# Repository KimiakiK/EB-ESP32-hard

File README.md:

# EB-ESP32
- [ESP32本体](https://github.com/KimiakiK/DIP-ESP32-hard)
- [ESP32用デバッガ](https://github.com/KimiakiK/DBG-ESP32-hard)
- [フルカラーLED付きロータリーエンコーダ](https://akizukidenshi.com/catalog/g/gP-05773/)
- [カラーディスプレイ TFT 1.3inch 240x240 ATM0130B3](https://akizukidenshi.com/catalog/g/gK-15560/)
- [キャラクタディスプレイ LCD 16x2 AQM1602Y-RN-GBW](https://akizukidenshi.com/catalog/g/gP-11916/)
- [温湿度・気圧センサ BME280](https://akizukidenshi.com/catalog/g/gK-09421/)
- [CO2センサ MH-Z19C](https://akizukidenshi.com/catalog/g/gM-16142/)
- [照度センサ NJL7502L](https://akizukidenshi.com/catalog/g/gI-02325/)
- [Micro SD カードコネクタ DM3AT-SF-PEJM5](https://akizukidenshi.com/catalog/g/gK-05488/)
- [リアルタイムクロック RTC IC RX8900 DIP AE-RX8900](https://akizukidenshi.com/catalog/g/gK-13009)

# Photos

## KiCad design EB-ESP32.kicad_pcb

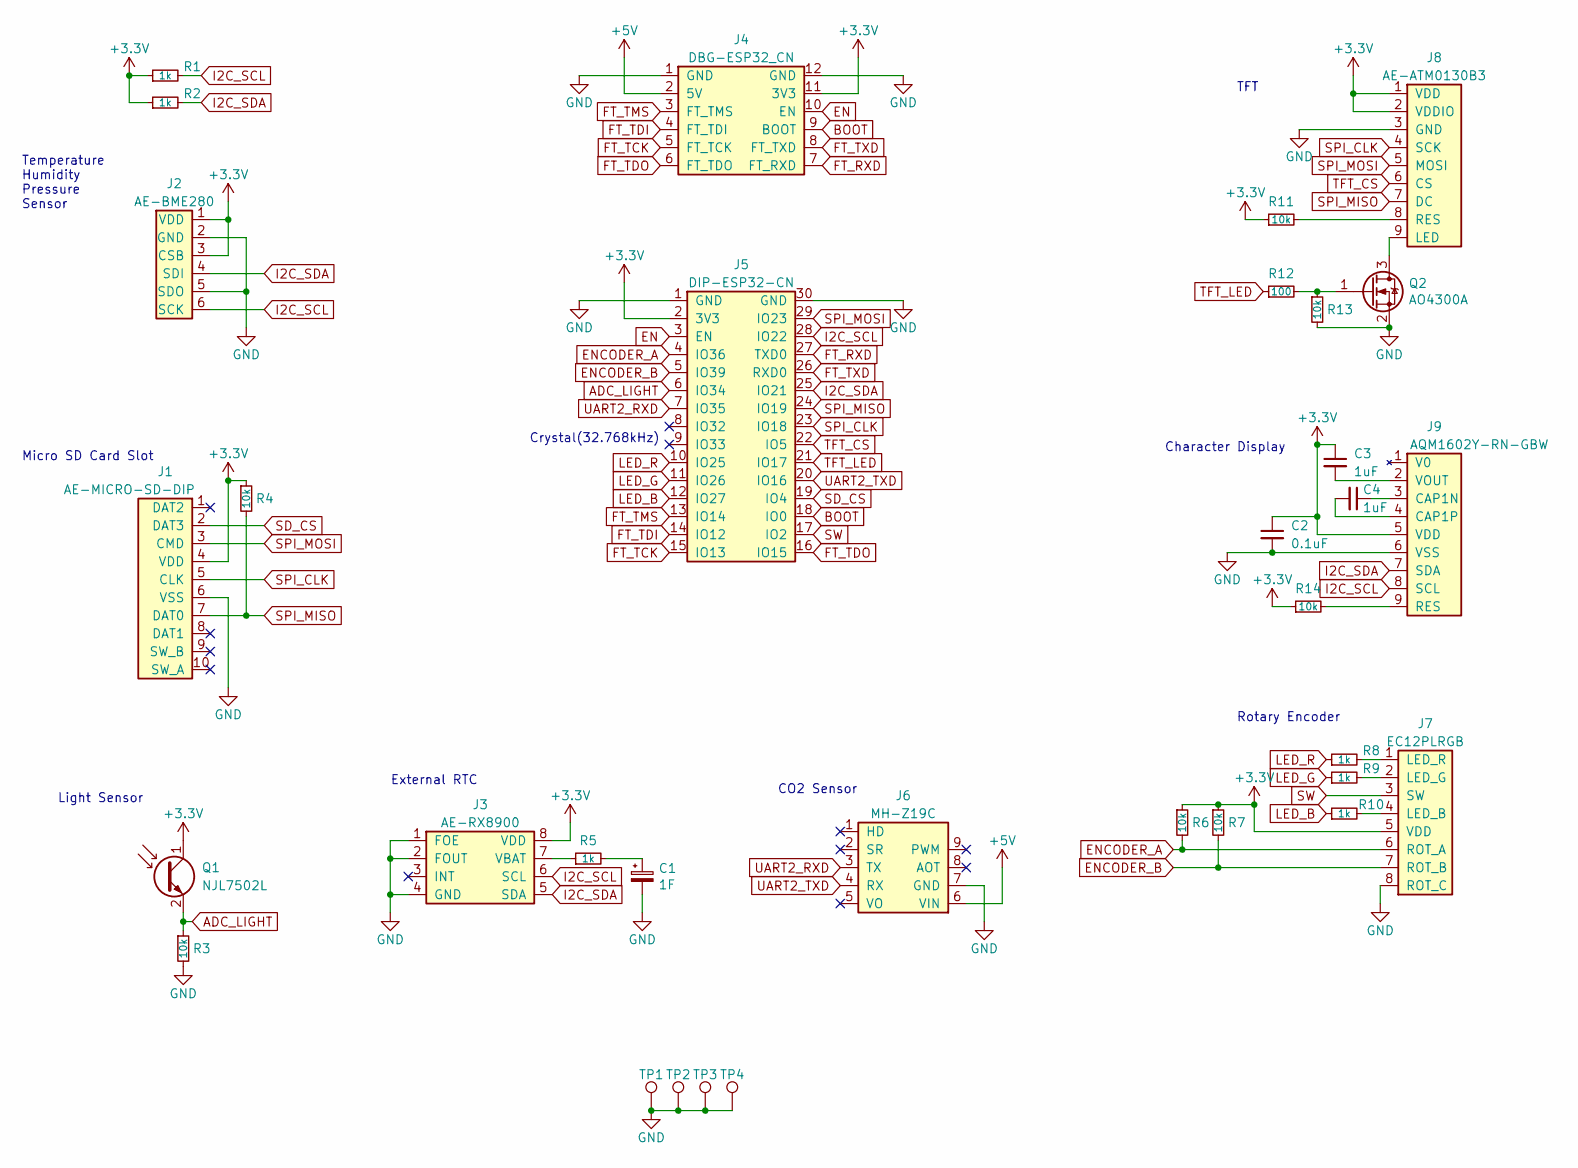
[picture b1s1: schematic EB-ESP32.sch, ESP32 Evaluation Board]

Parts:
C1: 1F; SE-5R5-D105VY
C2: 0.1uF; 1608Metric
C3, C4: 1uF; 1608Metric
J1: AE-MICRO-SD-DIP
J2: AE-BME280
J3: AE-RX8900
J4: DBG-ESP32_CN; DBG-ESP32-CN
J5: DIP-ESP32-CN
J6: MH-Z19C
J7: EC12PLRGB
J8: AE-ATM0130B3
J9: AQM1602Y-RN-GBW
Q1: NJL7502L
Q2: AO4300A; SOT-23
R1, R2, R5, R8, R9, R10: 1k; 1608Metric
R3, R4, R6, R7, R11, R13, R14: 10k; 1608Metric
R12: 100; 1608Metric
TP1, TP2, TP3, TP4: TestPoint; GND_PAD

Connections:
+3V3: C2.1, C3.1, J1.4 (VDD), J2.1 (VDD), J2.3 (CSB), J3.8 (VDD), J4.11 (3V3), J5.2 (3V3), J7.5 (VDD), J8.1 (VDD), J8.2 (VDDIO), J9.5 (VDD), Q1.1 (C), R1.1, R2.1, R4.1, R6.1, R7.1, R11.1, R14.1
+5V: J4.2 (5V), J6.6 (VIN)
ADC_LIGHT: J5.6 (IO34), Q1.2 (E), R3.1
BOOT: J4.9 (BOOT), J5.18 (IO0)
EN: J4.10 (EN), J5.3 (EN)
ENCODER_A: J5.4 (IO36), J7.6 (ROT_A), R6.2
ENCODER_B: J5.5 (IO39), J7.7 (ROT_B), R7.2
FT_RXD: J4.7 (FT_RXD), J5.27 (TXD0)
FT_TCK: J4.5 (FT_TCK), J5.15 (IO13)
FT_TDI: J4.4 (FT_TDI), J5.14 (IO12)
FT_TDO: J4.6 (FT_TDO), J5.16 (IO15)
FT_TMS: J4.3 (FT_TMS), J5.13 (IO14)
FT_TXD: J4.8 (FT_TXD), J5.26 (RXD0)
GND: C1.2, C2.2, J1.6 (VSS), J2.2 (GND), J2.5 (SDO), J3.1 (FOE), J3.2 (FOUT), J3.4 (GND), J4.1 (GND), J4.12 (GND), J5.1 (GND), J5.30 (GND), J6.7 (GND), J7.8 (ROT_C), J8.3 (GND), J9.6 (VSS), Q2.2 (S), R3.2, R13.2, TP1.1, TP2.1, TP3.1, TP4.1
I2C_SCL: J2.6 (SCK), J3.6 (SCL), J5.28 (IO22), J9.8 (SCL), R1.2
I2C_SDA: J2.4 (SDI), J3.5 (SDA), J5.25 (IO21), J9.7 (SDA), R2.2
LED_B: J5.12 (IO27), R10.1
LED_G: J5.11 (IO26), R9.1
LED_R: J5.10 (IO25), R8.1
unnamed: C1.1, R5.2
unnamed: C3.2, J9.2 (VOUT)
unnamed: C4.1, J9.3 (CAP1N)
unnamed: C4.2, J9.4 (CAP1P)
unnamed: J3.7 (VBAT), R5.1
unnamed: J7.1 (LED_R), R8.2
unnamed: J7.2 (LED_G), R9.2
unnamed: J7.4 (LED_B), R10.2
unnamed: J8.8 (RES), R11.2
unnamed: J8.9 (LED), Q2.3 (D)
unnamed: J9.9 (RES), R14.2
unnamed: Q2.1 (G), R12.2, R13.1
SD_CS: J1.2 (DAT3), J5.19 (IO4)
SPI_CLK: J1.5 (CLK), J5.23 (IO18), J8.4 (SCK)
SPI_MISO: J1.7 (DAT0), J5.24 (IO19), J8.7 (DC), R4.2
SPI_MOSI: J1.3 (CMD), J5.29 (IO23), J8.5 (MOSI)
SW: J5.17 (IO2), J7.3 (SW)
TFT_CS: J5.22 (IO5), J8.6 (CS)
TFT_LED: J5.21 (IO17), R12.1
UART2_RXD: J5.7 (IO35), J6.3 (TX)
UART2_TXD: J5.20 (IO16), J6.4 (RX)

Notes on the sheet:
Temperature Humidity Pressure Sensor
Micro SD Card Slot
Light Sensor
External RTC
CO2 Sensor
TFT
Character Display
Rotary Encoder
Crystal(32.768kHz)

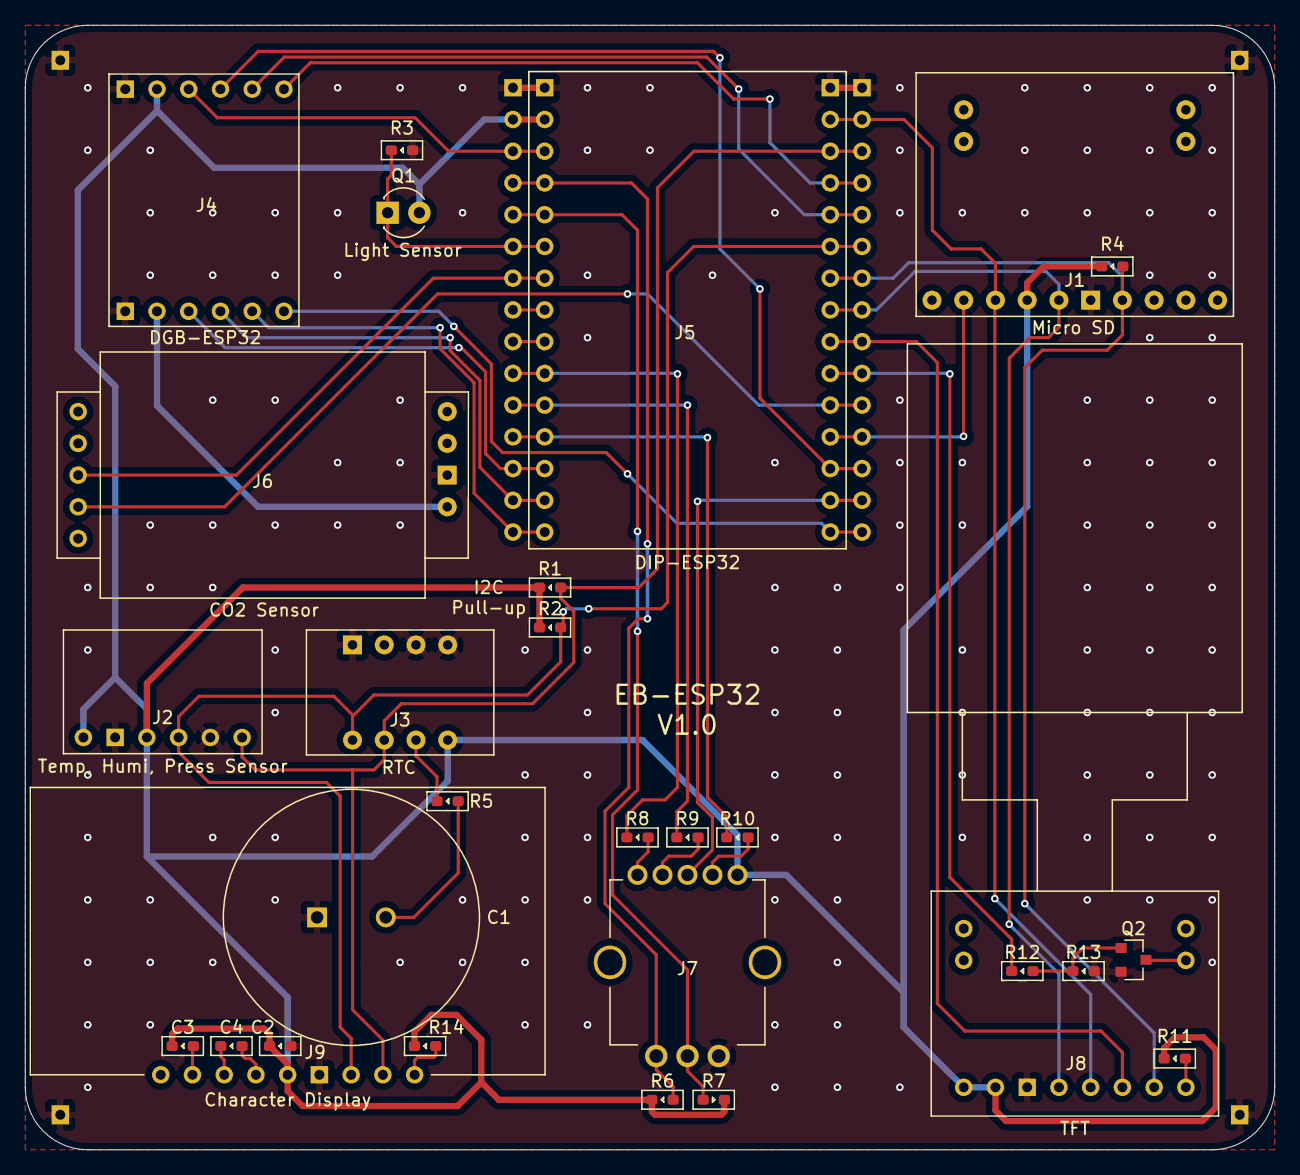
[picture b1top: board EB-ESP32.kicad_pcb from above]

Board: 2 copper layers, 100.0 x 90.0 mm, 33 parts (0 on the bottom side), 40 nets.

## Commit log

2021-12-01 基板 V1.0
2021-12-12 Add image
